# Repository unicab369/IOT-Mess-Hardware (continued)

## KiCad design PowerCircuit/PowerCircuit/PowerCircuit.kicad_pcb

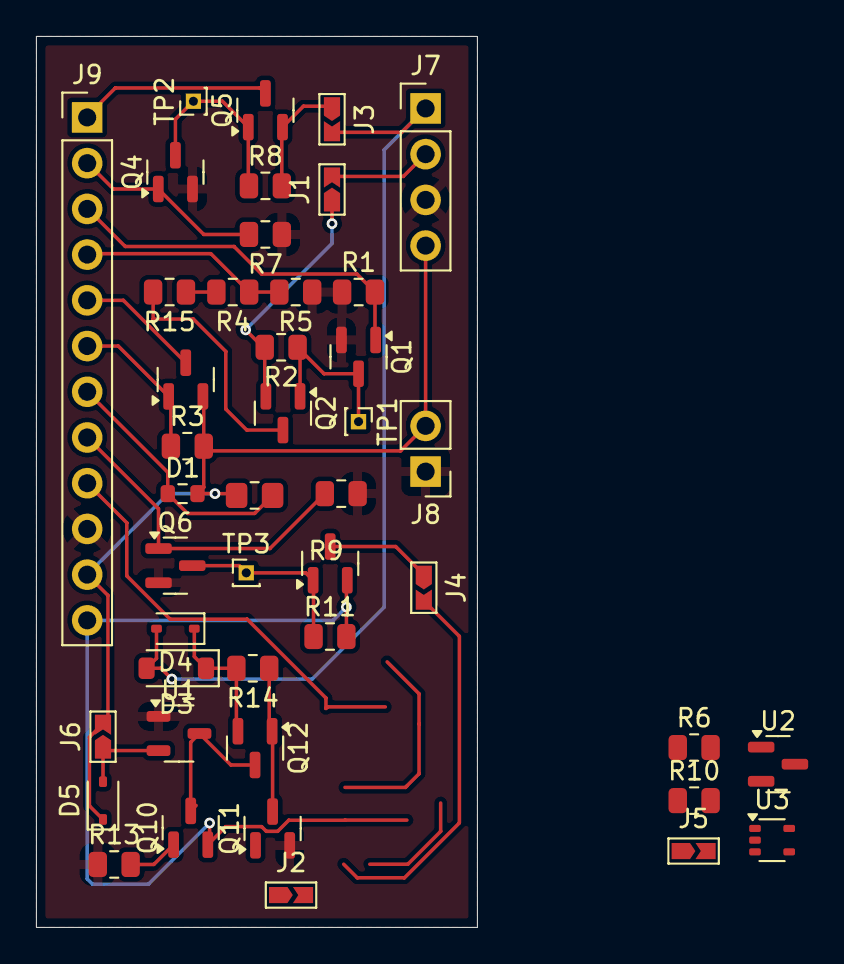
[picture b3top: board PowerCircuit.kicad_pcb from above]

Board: 2 copper layers, 24.5 x 49.5 mm, 44 parts (0 on the bottom side), 29 nets.

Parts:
D1: D_Photo; R_0603_1608Metric
D2: D_Photo; R_0805_2012Metric_Pad1.20x1.40mm_HandSolder
D3: MBR0520; D_SOD-123
D4, D5: BAT48JFILM; D_SOD-323
J1, J2, J3, J4, J5, J6: Jumper_2; Jumpper-triangle
J7: Conn_01x04_Pin; PinHeader_1x04_P2.54mm_Vertical
J8: Conn_01x02_Pin; PinHeader_1x02_P2.54mm_Vertical
J9: Conn_01x12_Pin; PinHeader_1x12_P2.54mm_Vertical
Q1, Q4, Q6, Q11: AO3400A; SOT-23
Q2, Q3, Q5, Q8, Q10, Q12: AO3401A (P-Fet); SOT-23
R1, R3, R7, R9, R10, R11, R13, R14: 100K; R_0805_2012Metric
R2, R4, R5, R6, R8, R15: 10K; R_0805_2012Metric
TP1, TP2, TP3: TestPoint; PinHeader_1x01_P1.00mm_Vertical
U1: XC6206PxxxMR; SOT-23-3
U2: LT431 (Voltage Ref); SOT-23
U3: 74LV1T08GW; SOT-353_SC-70-5

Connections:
+3V8: D1.2 (A), D2.2 (A), D5.1 (K), J6.2 (B), J7.4, J8.2, J9.11, Q3.2 (S), R3.2
ADC_LUX: D1.1 (K), D2.1 (K), J9.7
ADC_SOLAR: J9.4, R4.1, R5.2
GND: J7.3, J8.1, J9.10, Q1.2 (S), Q4.2 (S), Q6.2 (S), Q11.2 (S), R1.1, R5.1, R7.1, R9.1, R10.1, R13.1, U1.1 (GND), U2.3 (GND), U3.3 (GND)
IN-: D3.2 (A), D4.2 (A), J1.2 (B), J3.2 (B), J7.1
unnamed: D3.1 (K), D4.1 (K), Q12.2 (S), R14.2
unnamed: D5.2 (A), J6.1 (A), U1.2 (VO)
unnamed: J1.1 (A), Q2.2 (S), R2.2
unnamed: J2.1 (A), J5.2 (B), Q10.1 (G), R13.2
unnamed: J2.2 (B), J4.2 (B), Q11.1 (G)
unnamed: J3.1 (A), Q5.2 (S), R8.2
unnamed: J4.1 (A), Q8.3 (D)
unnamed: J5.1 (A), U3.4 (Y)
unnamed: Q1.3 (D), Q2.1 (G), R2.1, TP1.1
unnamed: Q2.3 (D), R15.2
unnamed: Q4.3 (D), Q5.1 (G), R8.1, TP2.1
unnamed: Q6.3 (D), Q8.1 (G), R11.1, TP3.1
unnamed: Q10.3 (D), Q12.3 (D), U1.3 (VI)
unnamed: Q11.3 (D), Q12.1 (G), R14.1
unnamed: R4.2, R15.1
unnamed: R6.2, U2.2 (VDD)
unnamed: R6.1, U2.1 (VOUT)
PWR_SENSORS: J9.5, Q3.3 (D)
SW_CHARGER: J9.2, Q4.1 (G), R7.2
SW_DIVIDER: J9.3, Q1.1 (G), R1.2
SW_PWR1: J9.8, Q6.1 (G), R9.2, R10.2, U3.2 (A)
SW_SENSORS: J9.6, Q3.1 (G), R3.1
TP4056_PWR: J9.1, Q5.3 (D)
VCC/BATT: J9.12, Q8.2 (S), Q10.2 (S), R11.2, U3.1 (B), U3.5 (VCC)

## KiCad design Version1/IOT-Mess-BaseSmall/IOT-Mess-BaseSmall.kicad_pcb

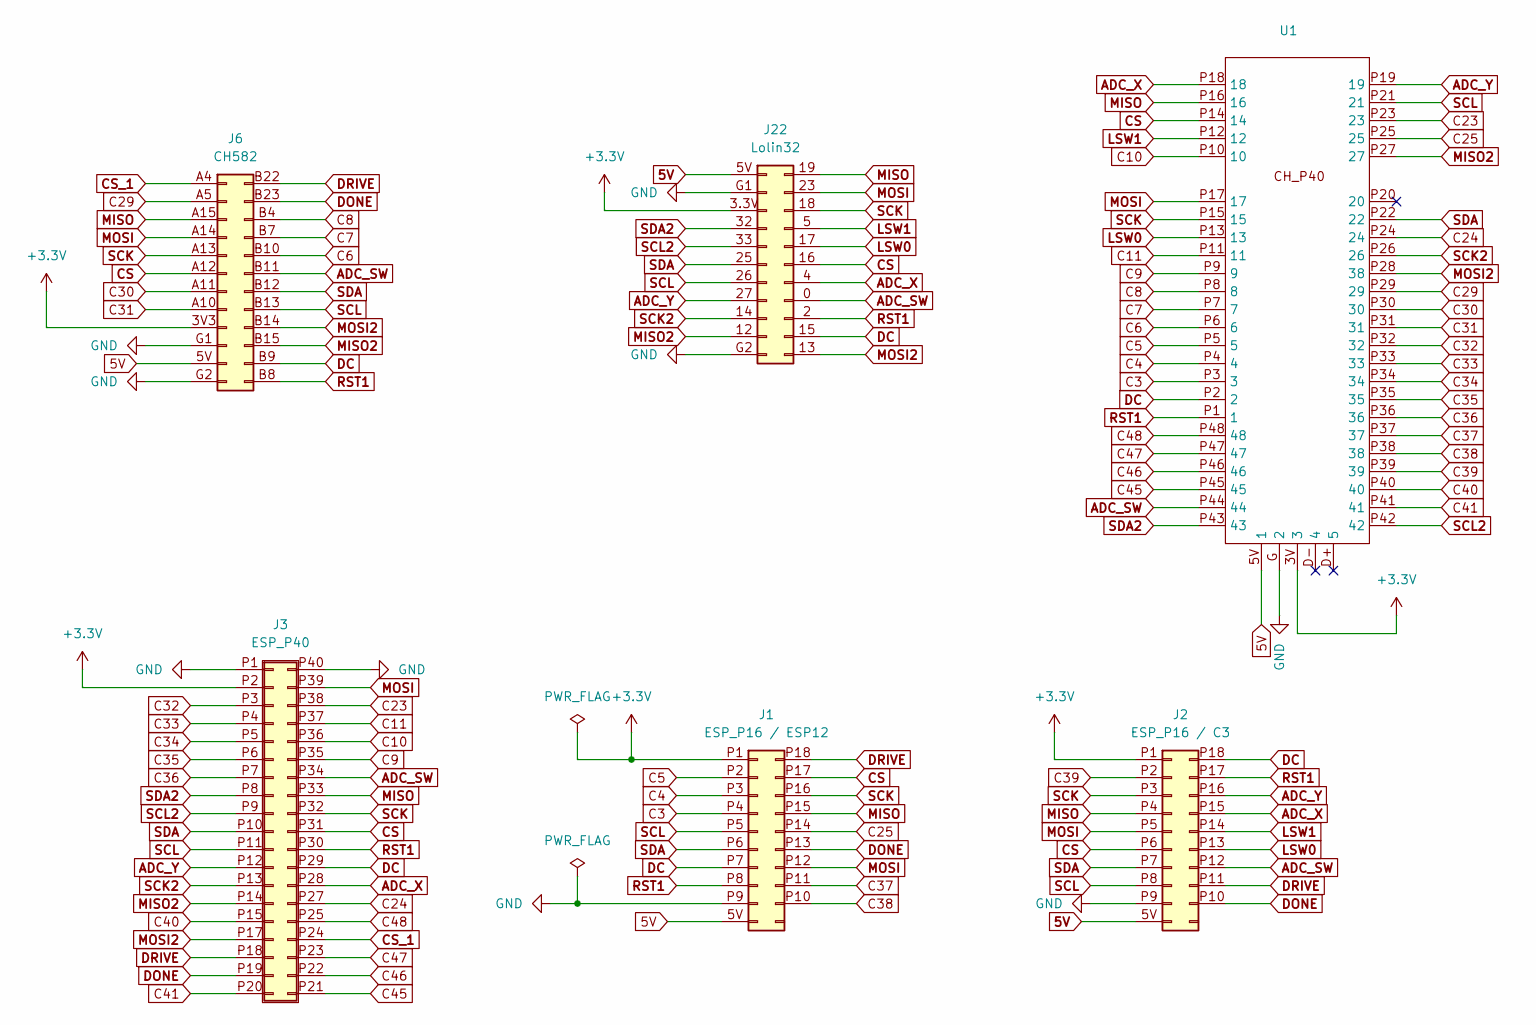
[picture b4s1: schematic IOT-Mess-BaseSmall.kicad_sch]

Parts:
J1: ESP_P16 / ESP12; ESP_P16
J2: ESP_P16 / C3; ESP_P16
J3: ESP_P40
J6: CH582; CH582_Base
J22: Lolin32; Lolin32-Adapter
U1: CH_P48

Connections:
5V: J1.5V (Pin_10), J2.5V (Pin_10), J6.5V (Pin_11), J22.5V (Pin_1), U1.5V (1)
+3.3V: J1.P1 (Pin_1), J2.P1 (Pin_1), J3.P2 (Pin_2), J6.3V3 (Pin_9), J22.3.3V (Pin_3), U1.3V (3)
ADC_SW: J2.P12 (Pin_14), J3.P34 (Pin_26), J6.B11 (Pin_18), J22.0 (Pin_19), U1.P44 (44)
ADC_X: J2.P15 (Pin_17), J3.P28 (Pin_32), J22.4 (Pin_18), U1.P18 (18)
ADC_Y: J2.P16 (Pin_18), J3.P12 (Pin_12), J22.27 (Pin_8), U1.P19 (19)
C3: J1.P4 (Pin_4), U1.P3 (3)
C4: J1.P3 (Pin_3), U1.P4 (4)
C5: J1.P2 (Pin_2), U1.P5 (5)
C6: J6.B10 (Pin_17), U1.P6 (6)
C7: J6.B7 (Pin_16), U1.P7 (7)
C8: J6.B4 (Pin_15), U1.P8 (8)
C9: J3.P35 (Pin_25), U1.P9 (9)
C10: J3.P36 (Pin_24), U1.P10 (10)
C11: J3.P37 (Pin_23), U1.P11 (11)
C23: J3.P38 (Pin_22), U1.P23 (23)
C24: J3.P27 (Pin_33), U1.P24 (24)
C25: J1.P14 (Pin_16), U1.P25 (25)
C29: J6.A5 (Pin_2), U1.P29 (29)
C30: J6.A11 (Pin_7), U1.P30 (30)
C31: J6.A10 (Pin_8), U1.P31 (31)
C32: J3.P3 (Pin_3), U1.P32 (32)
C33: J3.P4 (Pin_4), U1.P33 (33)
C34: J3.P5 (Pin_5), U1.P34 (34)
C35: J3.P6 (Pin_6), U1.P35 (35)
C36: J3.P7 (Pin_7), U1.P36 (36)
C37: J1.P11 (Pin_13), U1.P37 (37)
C38: J1.P10 (Pin_12), U1.P38 (38)
C39: J2.P2 (Pin_2), U1.P39 (39)
C40: J3.P15 (Pin_15), U1.P40 (40)
C41: J3.P20 (Pin_19), U1.P41 (41)
C45: J3.P21 (Pin_38), U1.P45 (45)
C46: J3.P22 (Pin_37), U1.P46 (46)
C47: J3.P23 (Pin_36), U1.P47 (47)
C48: J3.P25 (Pin_34), U1.P48 (48)
CS: J1.P17 (Pin_19), J2.P6 (Pin_6), J3.P31 (Pin_29), J6.A12 (Pin_6), J22.16 (Pin_17), U1.P14 (14)
CS_1: J3.P24 (Pin_35), J6.A4 (Pin_1)
DC: J1.P7 (Pin_7), J2.P18 (Pin_20), J3.P29 (Pin_31), J6.B9 (Pin_23), J22.15 (Pin_21), U1.P2 (2)
DONE: J1.P13 (Pin_15), J2.P10 (Pin_12), J3.P19 (Pin_18), J6.B23 (Pin_14)
DRIVE: J1.P18 (Pin_20), J2.P11 (Pin_13), J3.P18 (Pin_17), J6.B22 (Pin_13)
GND: J1.P9 (Pin_9), J2.P9 (Pin_9), J3.P1 (Pin_1), J3.P40 (Pin_20), J6.G1 (Pin_10), J6.G2 (Pin_12), J22.G1 (Pin_2), J22.G2 (Pin_11), U1.G (2)
LSW0: J2.P13 (Pin_15), J22.17 (Pin_16), U1.P13 (13)
LSW1: J2.P14 (Pin_16), J22.5 (Pin_15), U1.P12 (12)
MISO: J1.P15 (Pin_17), J2.P4 (Pin_4), J3.P33 (Pin_27), J6.A15 (Pin_3), J22.19 (Pin_12), U1.P16 (16)
MISO2: J3.P14 (Pin_14), J6.B15 (Pin_22), J22.12 (Pin_10), U1.P27 (27)
MOSI: J1.P12 (Pin_14), J2.P5 (Pin_5), J3.P39 (Pin_21), J6.A14 (Pin_4), J22.23 (Pin_13), U1.P17 (17)
MOSI2: J3.P17 (Pin_16), J6.B14 (Pin_21), J22.13 (Pin_22), U1.P28 (38)
RST1: J1.P8 (Pin_8), J2.P17 (Pin_19), J3.P30 (Pin_30), J6.B8 (Pin_24), J22.2 (Pin_20), U1.P1 (1)
SCK: J1.P16 (Pin_18), J2.P3 (Pin_3), J3.P32 (Pin_28), J6.A13 (Pin_5), J22.18 (Pin_14), U1.P15 (15)
SCK2: J3.P13 (Pin_13), J22.14 (Pin_9), U1.P26 (26)
SCL: J1.P5 (Pin_5), J2.P8 (Pin_8), J3.P11 (Pin_11), J6.B13 (Pin_20), J22.26 (Pin_7), U1.P21 (21)
SCL2: J3.P9 (Pin_9), J22.33 (Pin_5), U1.P42 (42)
SDA: J1.P6 (Pin_6), J2.P7 (Pin_7), J3.P10 (Pin_10), J6.B12 (Pin_19), J22.25 (Pin_6), U1.P22 (22)
SDA2: J3.P8 (Pin_8), J22.32 (Pin_4), U1.P43 (43)

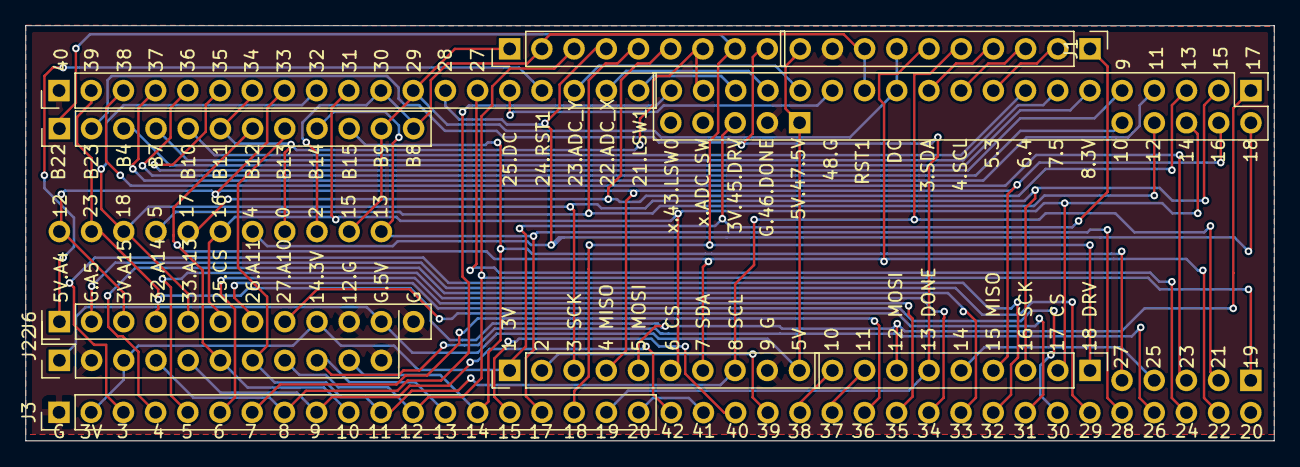
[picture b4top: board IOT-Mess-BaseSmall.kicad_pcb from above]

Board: 2 copper layers, 98.5 x 32.8 mm, 6 parts (0 on the bottom side), 53 nets.

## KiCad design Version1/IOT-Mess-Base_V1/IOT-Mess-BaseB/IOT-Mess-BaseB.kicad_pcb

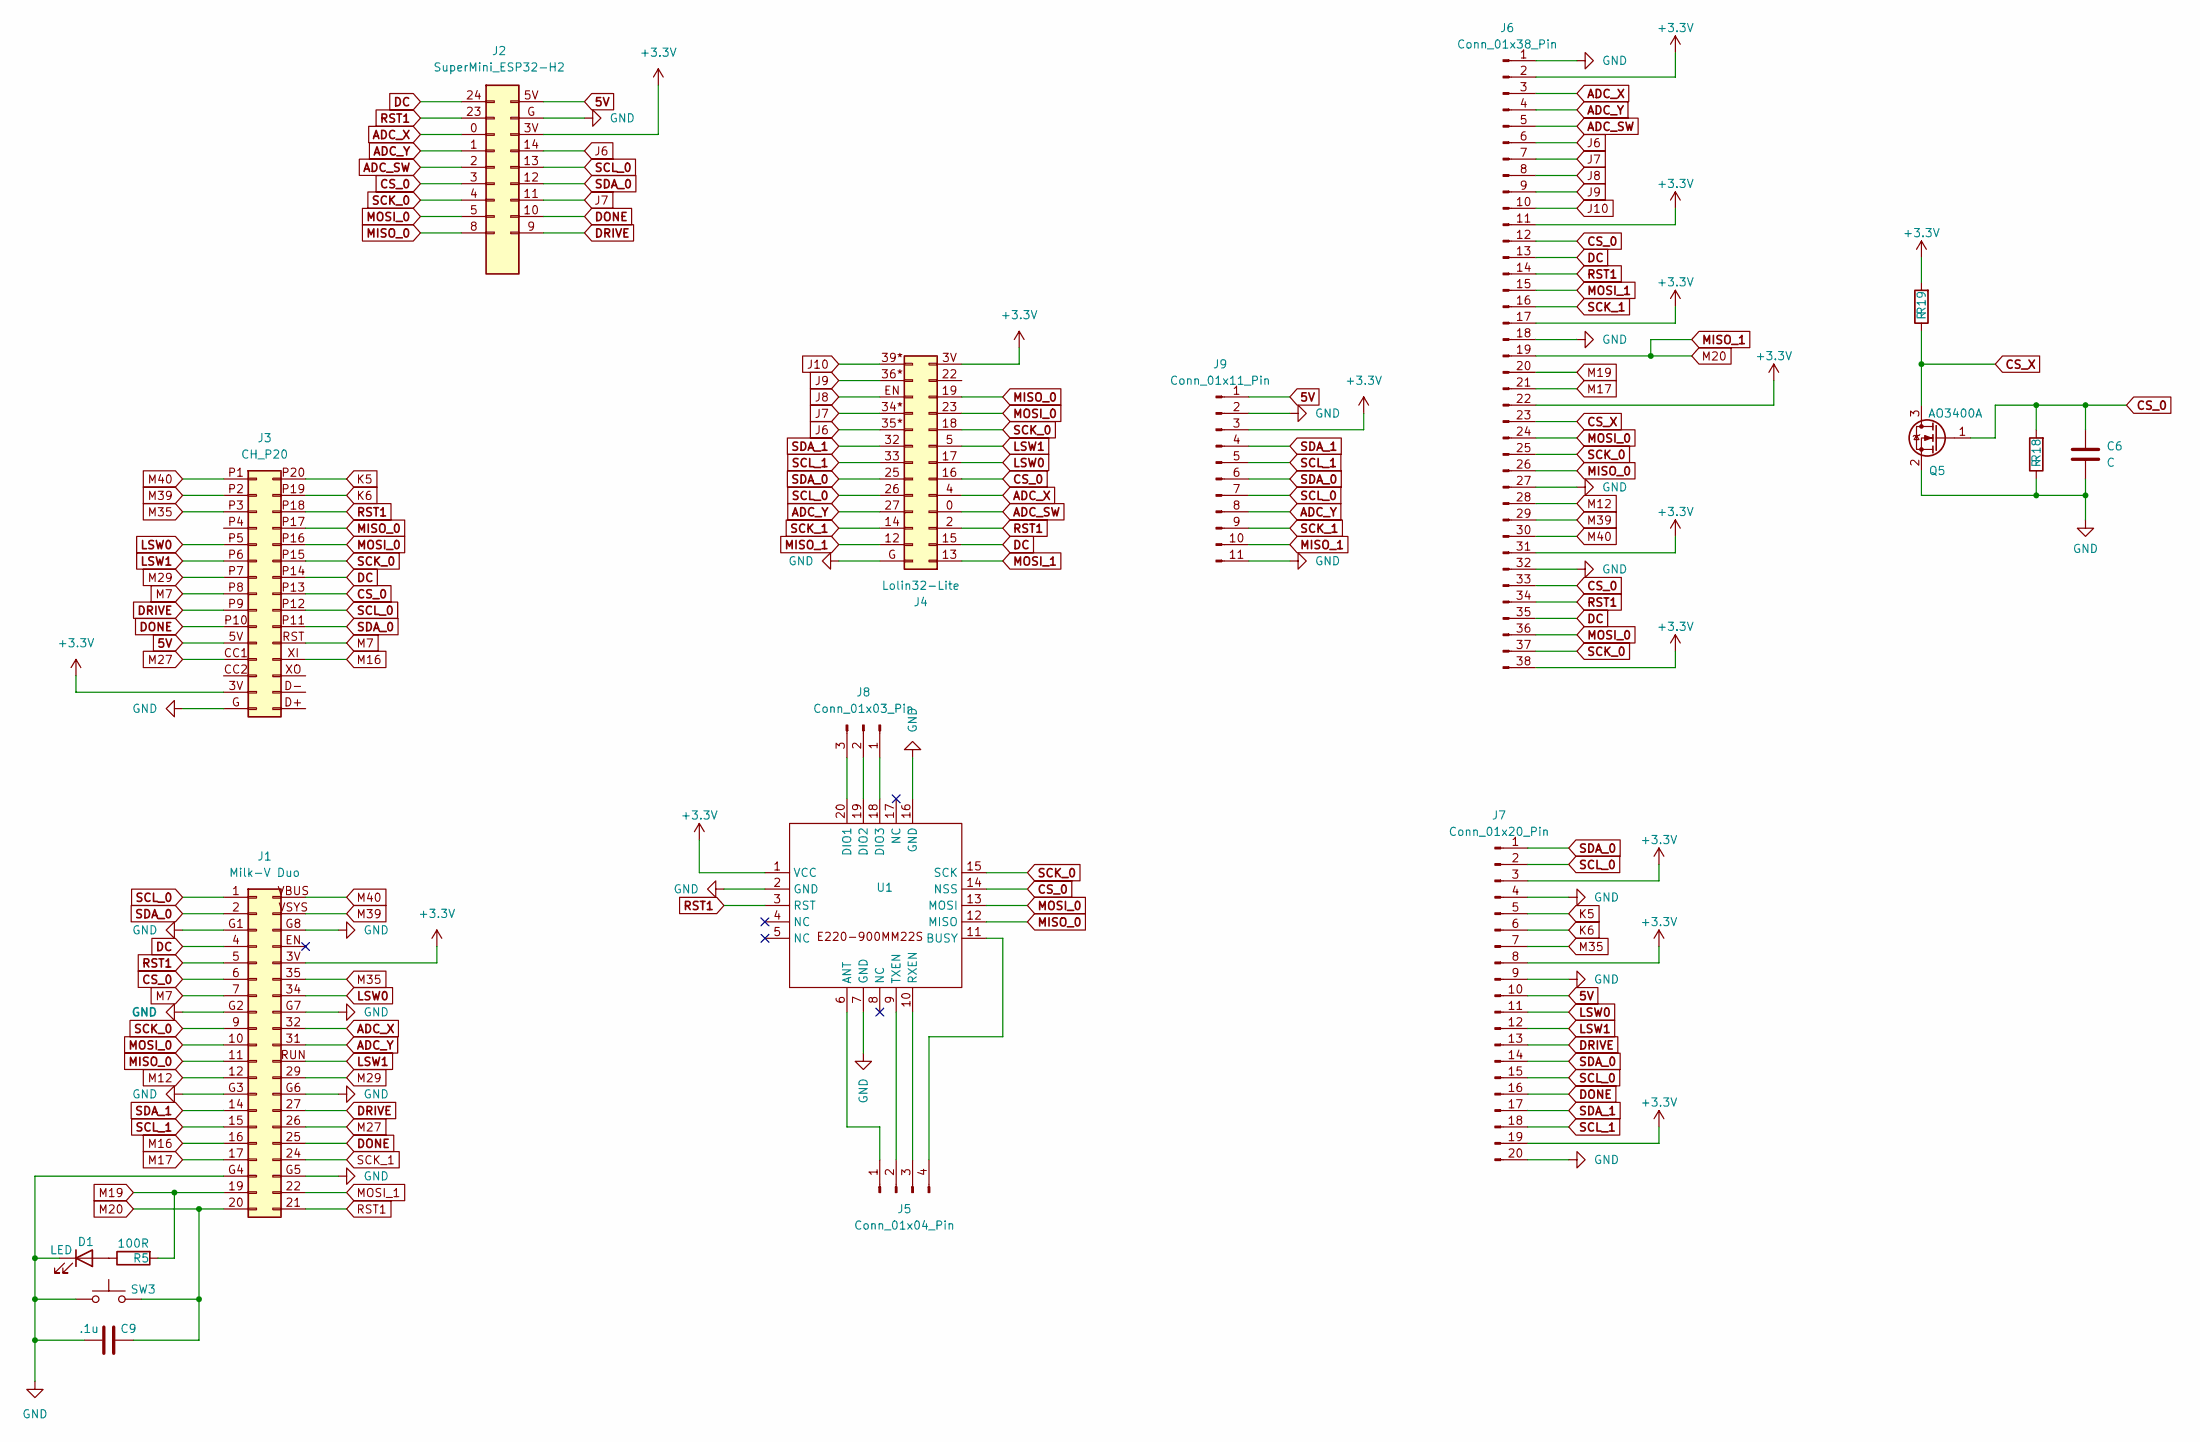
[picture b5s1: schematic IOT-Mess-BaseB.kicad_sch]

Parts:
C6: C; C_0603_1608Metric
C9: .1u; C_0603_1608Metric
D1: LED; LED_0603_1608Metric
J1: Milk-V Duo
J2: SuperMini_ESP32-H2; SuperMiniH2
J3: CH_P20
J4: Lolin32-Lite
J5: Conn_01x04_Pin; PinHeader_1x04_P1.27mm_Vertical
J6: Conn_01x38_Pin; PinHeader_1x38_P2.54mm_Vertical
J7: Conn_01x20_Pin; PinHeader_1x20_P2.54mm_Vertical
J8: Conn_01x03_Pin; PinHeader_1x03_P1.27mm_Vertical
J9: Conn_01x11_Pin; PinHeader_1x11_P2.54mm_Vertical
Q5: AO3400A; SOT-23
R5: 100R; R_0603_1608Metric
R18, R19: R; R_0603_1608Metric
SW3: SW_Push; SW_SPST_PTS810
U1: E220-900

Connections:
5V: J2.5V (Pin_18), J3.5V (Pin_11), J7.10, J9.1
+3.3V: J1.3V (Pin_36), J2.3V (Pin_16), J3.3V (Pin_14), J4.3V (Pin_13a), J6.2, J6.11, J6.17, J6.22, J6.31, J6.38, J7.3, J7.8, J7.19, J9.3, R19.2, U1.1 (VCC)
ADC_SW: J2.2 (Pin_5), J4.0 (Pin_4a), J6.5
ADC_X: J1.32, J2.0 (Pin_3), J4.4 (Pin_5a), J6.3
ADC_Y: J1.31, J2.1 (Pin_4), J4.27 (Pin_4b), J6.4, J9.8
CS_0: C6.1, J1.6, J2.3 (Pin_6), J3.P13 (Pin_23), J4.16 (Pin_6a), J6.12, J6.33, Q5.1 (G), R18.2, U1.14 (NSS)
CS_X: J6.23, Q5.3 (D), R19.1
DC: J1.4, J2.24 (Pin_1), J3.P14 (Pin_22), J4.15 (Pin_2a), J6.13, J6.35
DONE: J1.25, J2.10 (Pin_11), J3.P10 (Pin_10), J7.16
DRIVE: J1.27, J2.9 (Pin_10), J3.P9 (Pin_9), J7.13
GND: C6.2, C9.1, D1.1 (K), J1.G1 (Pin_3), J1.G2 (Pin_8), J1.G3 (Pin_13), J1.G4 (Pin_18), J1.G5 (Pin_23), J1.G6 (Pin_28), J1.G7 (Pin_33), J1.G8 (Pin_38), J2.G (Pin_17), J3.G (Pin_15), J4.G (Pin_1b), J6.1, J6.18, J6.27, J6.32, J7.4, J7.9, J7.20, J9.2, J9.11, Q5.2 (S), R18.1, SW3.2, U1.2 (GND), U1.7 (GND), U1.16 (GND)
J6: J2.14 (Pin_15), J4.35* (Pin_9b), J6.6
J7: J2.11 (Pin_12), J4.34* (Pin_10b), J6.7
J8: J4.EN (Pin_11b), J6.8
J9: J4.36* (Pin_12b), J6.9
J10: J4.39* (Pin_13b), J6.10
K5: J3.P20 (Pin_16), J7.5
K6: J3.P19 (Pin_17), J7.6
LSW0: J1.34, J2.26 (Pin_2), J3.P5 (Pin_5), J4.17 (Pin_7a), J7.11
LSW1: J1.RUN (Pin_30), J2.27 (Pin_1), J3.P6 (Pin_6), J4.5 (Pin_8a), J7.12
M7: J1.7, J3.P8 (Pin_8), J3.RST (Pin_26)
M12: J1.12, J6.28
M16: J1.16, J3.XI (Pin_27)
M17: J1.17, J6.21
M19: J1.19, J6.20, R5.2
M20: C9.2, J1.20, J4.12 (Pin_2b), J6.19, J9.10, SW3.1
M27: J1.26, J3.CC1 (Pin_12)
M29: J1.29, J3.P7 (Pin_7)
M35: J1.35, J3.P3 (Pin_3), J7.7
M39: J1.VSYS (Pin_39), J3.P2 (Pin_2), J6.29
M40: J1.VBUS (Pin_40), J3.P1 (Pin_1), J6.30
MISO_0: J1.11, J2.8 (Pin_9), J3.P17 (Pin_19), J4.19 (Pin_11a), J6.26, U1.12 (MISO)
MOSI_0: J1.10, J2.5 (Pin_8), J3.P16 (Pin_20), J4.23 (Pin_10a), J6.24, J6.36, U1.13 (MOSI)
MOSI_1: J1.22, J4.13 (Pin_1a), J6.15
unnamed: D1.2 (A), R5.1
unnamed: J5.1, U1.6 (ANT)
unnamed: J5.2, U1.9 (TXEN)
unnamed: J5.3, U1.10 (RXEN)
unnamed: J5.4, U1.11 (BUSY)
unnamed: J8.1, U1.18 (DIO3)
unnamed: J8.2, U1.19 (DIO2)
unnamed: J8.3, U1.20 (DIO1)
RST1: J1.5, J1.21, J2.23 (Pin_2), J3.P18 (Pin_18), J4.2 (Pin_3a), J6.14, J6.34, U1.3 (RST)
SCK_0: J1.9, J2.4 (Pin_7), J3.P15 (Pin_21), J4.18 (Pin_9a), J6.25, J6.37, U1.15 (SCK)
SCK_1: J1.24, J4.14 (Pin_3b), J6.16, J9.9
SCL_0: J1.1, J2.13 (Pin_14), J3.P12 (Pin_24), J4.26 (Pin_5b), J7.2, J7.15, J9.7
SCL_1: J1.15, J4.33 (Pin_7b), J7.18, J9.5
SDA_0: J1.2, J2.12 (Pin_13), J3.P11 (Pin_25), J4.25 (Pin_6b), J7.1, J7.14, J9.6
SDA_1: J1.14, J4.32 (Pin_8b), J7.17, J9.4

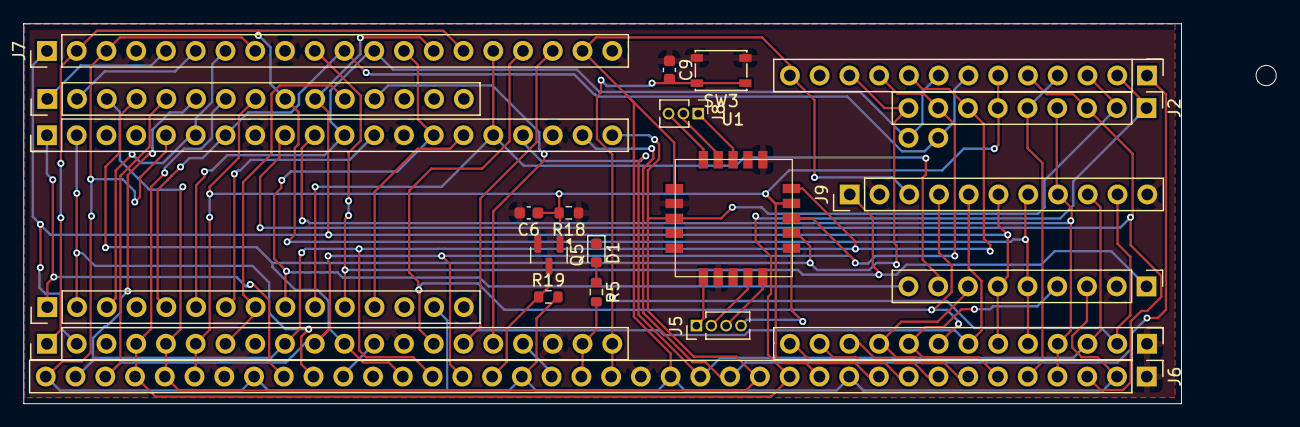
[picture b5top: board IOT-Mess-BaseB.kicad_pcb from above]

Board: 2 copper layers, 106.9 x 32.4 mm, 18 parts (0 on the bottom side), 49 nets.

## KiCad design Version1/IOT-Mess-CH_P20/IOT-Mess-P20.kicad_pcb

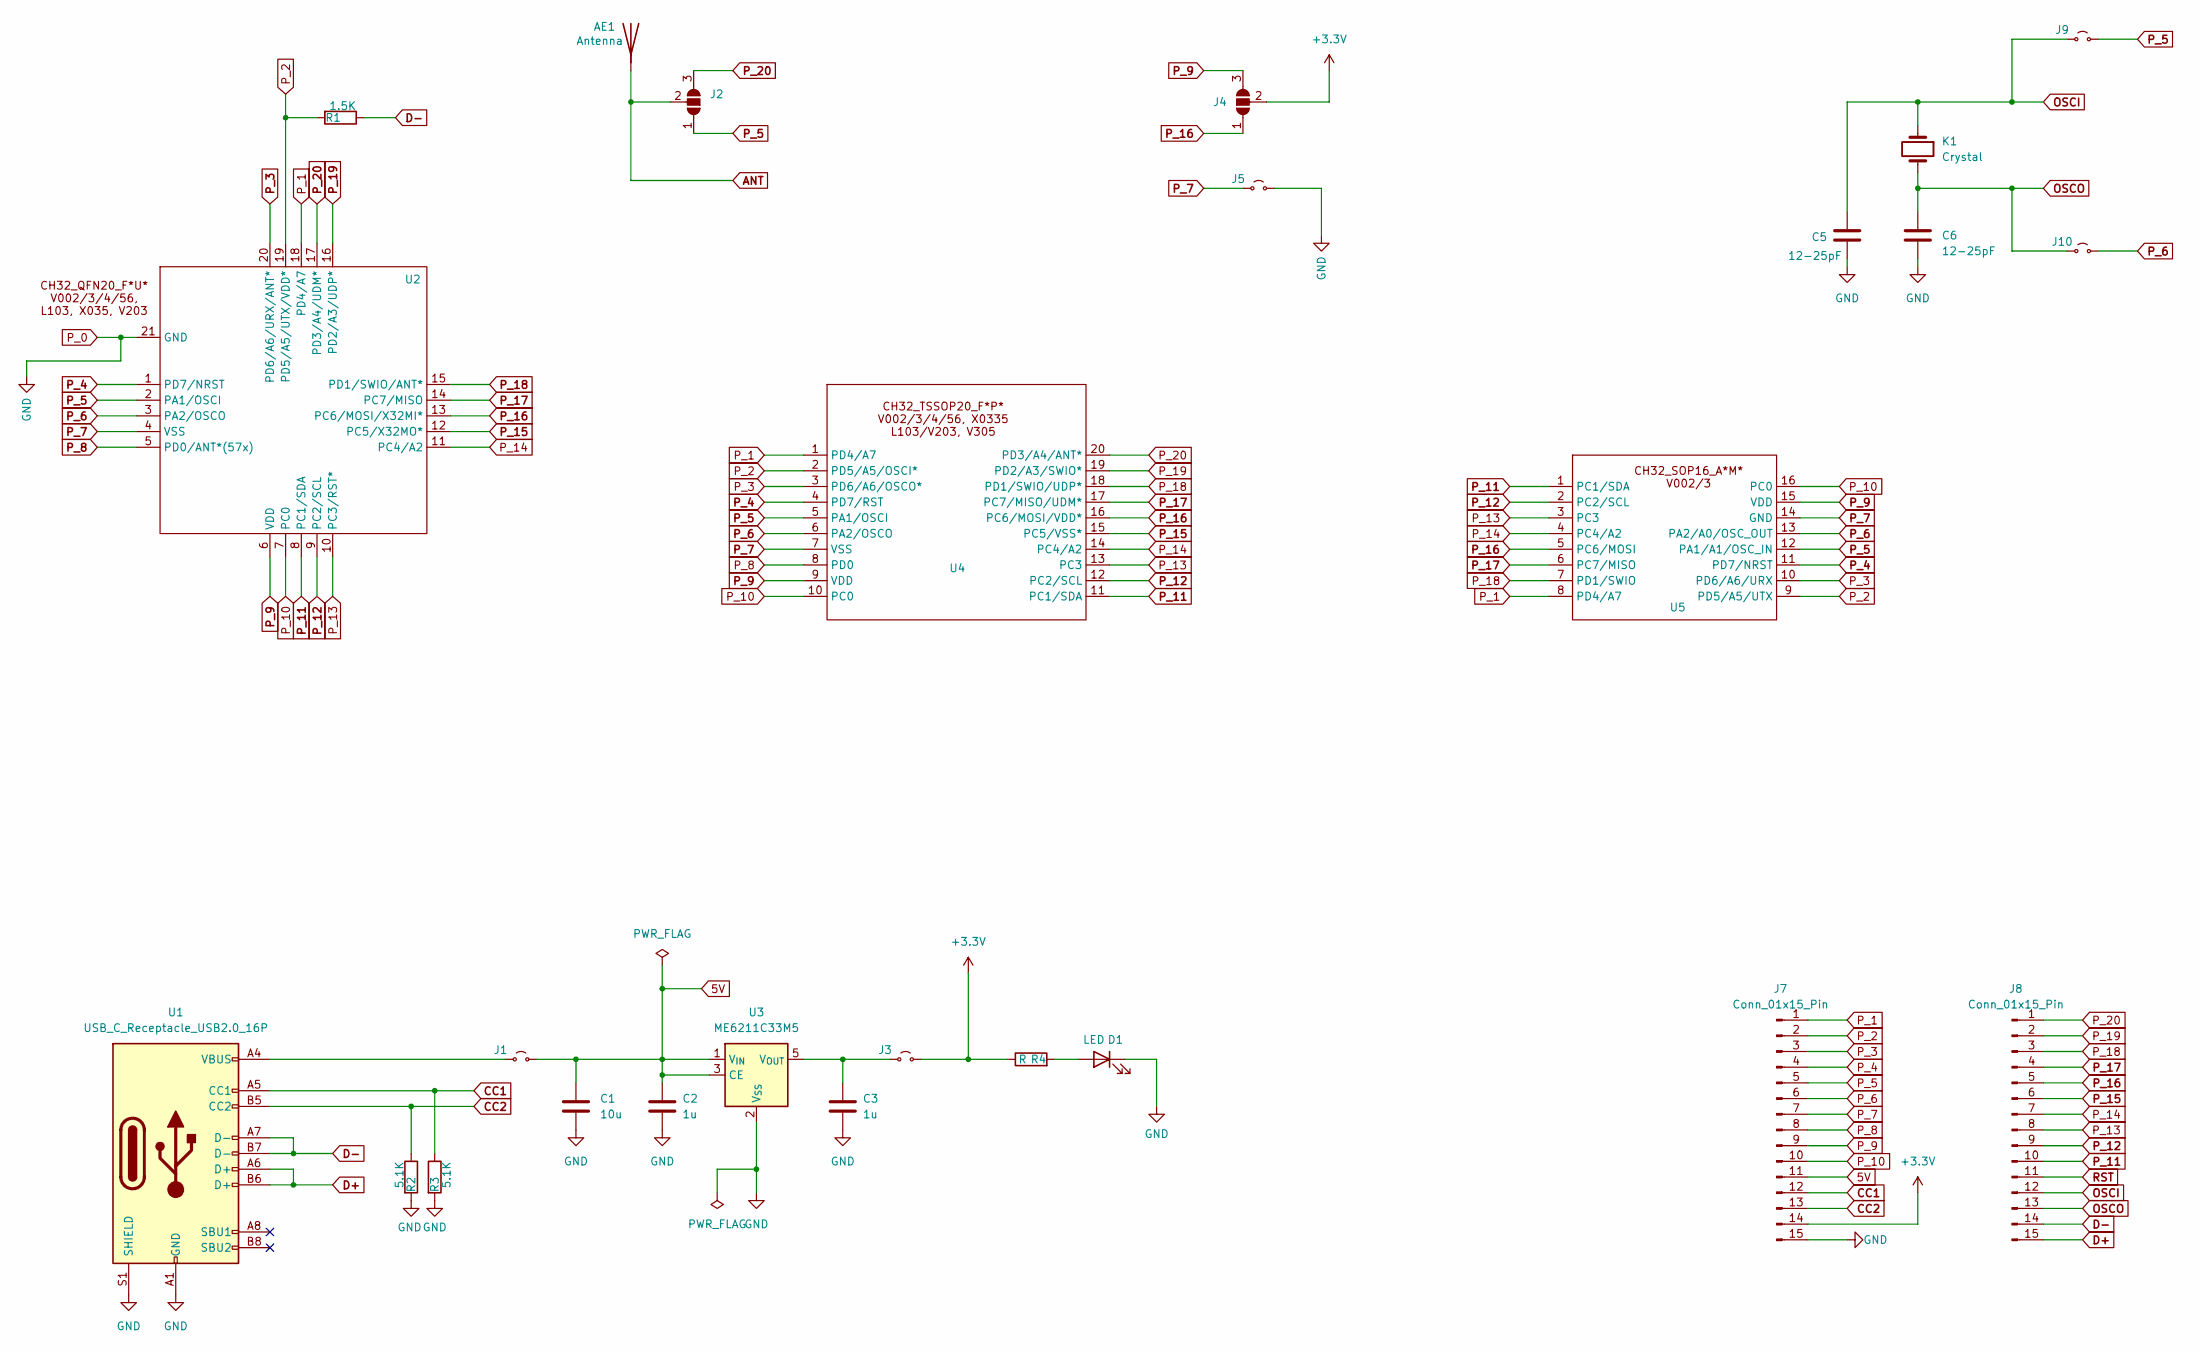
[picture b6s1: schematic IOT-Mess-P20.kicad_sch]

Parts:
AE1: Antenna; Texas_SWRA117D_2.4GHz_Right
C1: 10u; C_0603_1608Metric
C2, C3: 1u; C_0603_1608Metric
C5, C6: 12-25pF; C_0603_1608Metric
D1: LED; LED_0603_1608Metric
J1, J3, J5, J9, J10: Jumper_2; Jumpper-triangle
J2, J4: Jumper; Jumper-3_P1.3mm_Open_RoundedPad1.0x1.5mm
J7, J8: Conn_01x15_Pin; PinHeader_1x15_P2.54mm_Vertical
K1: Crystal; Crystal_SMD_3225-4Pin_3.2x2.5mm
R1: 1.5K; R_0603_1608Metric
R2, R3: 5.1K; R_0603_1608Metric
R4: R; R_0603_1608Metric
U1: USB_C_Receptacle_USB2.0_16P; USB_C_Receptacle_HRO_TYPE-C-31-M-12
U2: QFN-20-1EP_3x3mm_P0.4mm_EP1.65x1.65mm_ThermalVias
U3: ME6211C33M5; SOT-23-5
U4: TSSOP-20_4.4x6.5mm_P0.65mm
U5: SOP-16_3.9x9.9mm_P1.27mm

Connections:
5V: C1.1, C2.1, J1.2 (B), J7.11, U3.1 (V_{IN}), U3.3 (CE)
+3.3V: J3.2 (B), J4.2 (C), J7.14, R4.1
ANT: AE1.1 (A), J2.2 (C)
CC1: J7.12, R3.1, U1.A5 (CC1)
CC2: J7.13, R2.1, U1.B5 (CC2)
D+: J8.15, U1.A6 (D+), U1.B6 (D+)
D-: J8.14, R1.1, U1.A7 (D-), U1.B7 (D-)
unnamed: D1.2 (A), R4.2
unnamed: J1.1 (A), U1.A4 (VBUS), U1.A9 (VBUS), U1.B4 (VBUS), U1.B9 (VBUS)
unnamed: C3.1, J3.1 (A), U3.5 (V_{OUT})
OSCI: C5.1, J8.12, J9.1 (A), K1.1
OSCO: C6.1, J8.13, J10.1 (A), K1.2
P_0: C1.2, C2.2, C3.2, C5.2, C6.2, D1.1 (K), J5.2 (B), J7.15, R2.2, R3.2, U1.A1 (GND), U1.A12 (GND), U1.B1 (GND), U1.B12 (GND), U1.S1 (SHIELD), U2.21 (GND), U3.2 (V_{SS})
P_1: J7.1, U2.18 (PD4/A7), U4.1 (PD4/A7), U5.8 (PD4/A7)
P_2: J7.2, R1.2, U2.19 (PD5/A5/UTX/VDD*), U4.2 (PD5/A5/OSCI*), U5.9 (PD5/A5/UTX)
P_3: J7.3, U2.20 (PD6/A6/URX/ANT*), U4.3 (PD6/A6/OSCO*), U5.10 (PD6/A6/URX)
P_4: J7.4, U2.1 (PD7/NRST), U4.4 (PD7/RST), U5.11 (PD7/NRST)
P_5: J2.1 (A), J7.5, J9.2 (B), U2.2 (PA1/OSCI), U4.5 (PA1/OSCI), U5.12 (PA1/A1/OSC_IN)
P_6: J7.6, J10.2 (B), U2.3 (PA2/OSCO), U4.6 (PA2/OSCO), U5.13 (PA2/A0/OSC_OUT)
P_7: J5.1 (A), J7.7, U2.4 (VSS), U4.7 (VSS), U5.14 (GND)
P_8: J7.8, U2.5 (PD0/ANT*(57x)), U4.8 (PD0)
P_9: J4.3 (B), J7.9, U2.6 (VDD), U4.9 (VDD), U5.15 (VDD)
P_10: J7.10, U2.7 (PC0), U4.10 (PC0), U5.16 (PC0)
P_11: J8.10, U2.8 (PC1/SDA), U4.11 (PC1/SDA), U5.1 (PC1/SDA)
P_12: J8.9, U2.9 (PC2/SCL), U4.12 (PC2/SCL), U5.2 (PC2/SCL)
P_13: J8.8, U2.10 (PC3/RST*), U4.13 (PC3), U5.3 (PC3)
P_14: J8.7, U2.11 (PC4/A2), U4.14 (PC4/A2), U5.4 (PC4/A2)
P_15: J8.6, U2.12 (PC5/X32MO*), U4.15 (PC5/VSS*)
P_16: J4.1 (A), J8.5, U2.13 (PC6/MOSI/X32MI*), U4.16 (PC6/MOSI/VDD*), U5.5 (PC6/MOSI)
P_17: J8.4, U2.14 (PC7/MISO), U4.17 (PC7/MISO/UDM*), U5.6 (PC7/MISO)
P_18: J8.3, U2.15 (PD1/SWIO/ANT*), U4.18 (PD1/SWIO/UDP*), U5.7 (PD1/SWIO)
P_19: J8.2, U2.16 (PD2/A3/UDP*), U4.19 (PD2/A3/SWIO*)
P_20: J2.3 (B), J8.1, U2.17 (PD3/A4/UDM*), U4.20 (PD3/A4/ANT*)
RST: J8.11

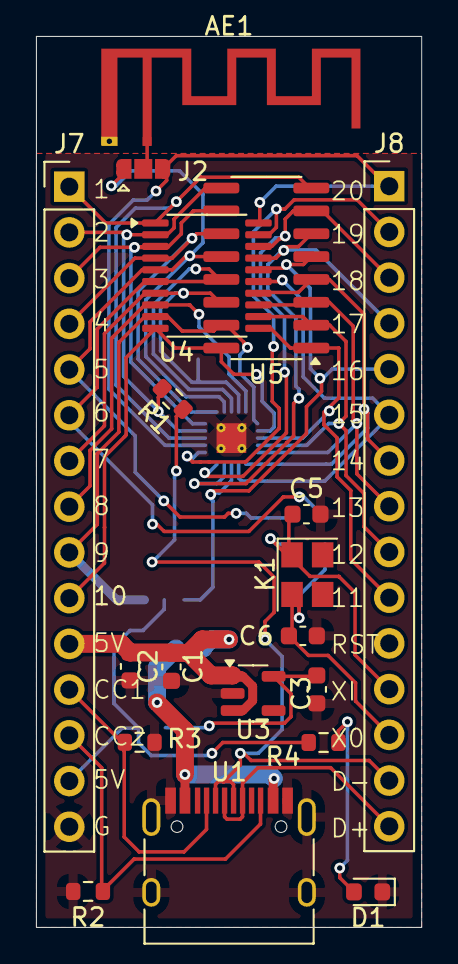
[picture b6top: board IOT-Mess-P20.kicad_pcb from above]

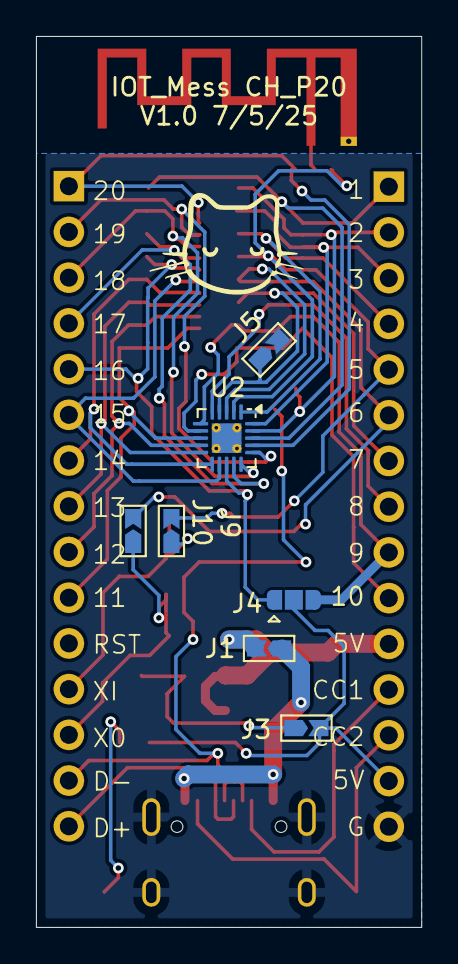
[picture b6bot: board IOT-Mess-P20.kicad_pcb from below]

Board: 2 copper layers, 21.4 x 49.5 mm, 26 parts (7 on the bottom side), 33 nets.

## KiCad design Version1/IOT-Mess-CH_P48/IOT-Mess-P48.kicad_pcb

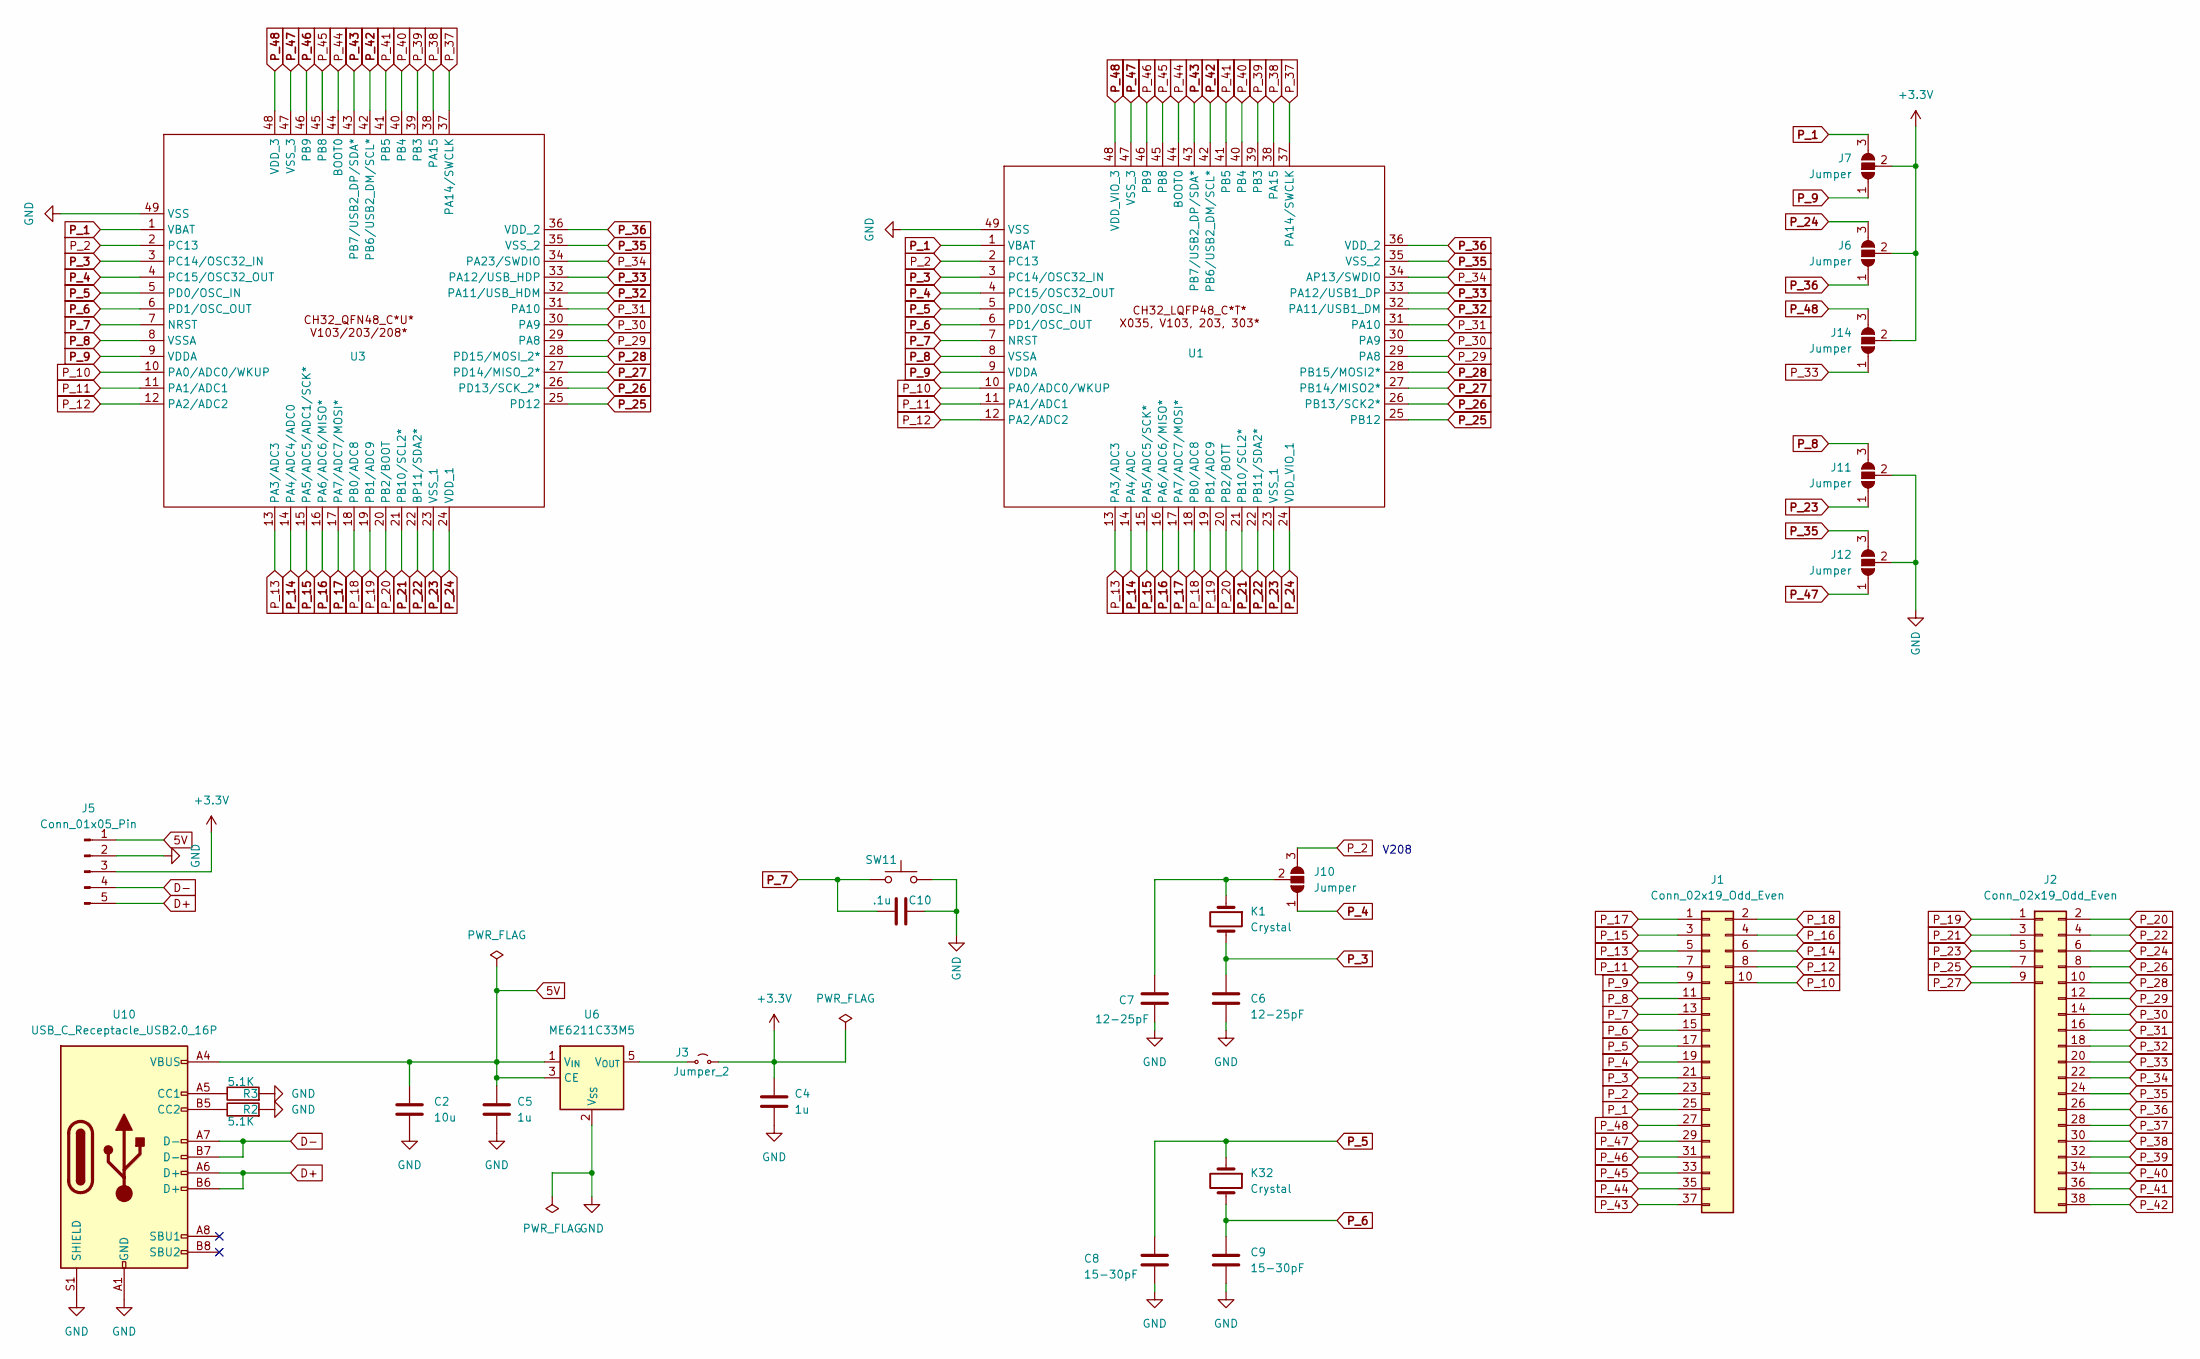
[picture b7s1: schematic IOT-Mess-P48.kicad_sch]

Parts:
C2: 10u; C_0603_1608Metric
C4, C5: 1u; C_0603_1608Metric
C6, C7: 12-25pF; C_0603_1608Metric
C8, C9: 15-30pF; C_0603_1608Metric
C10: .1u; C_0603_1608Metric
J1, J2: Conn_02x19_Odd_Even; PinHeader_2x19_P2.54mm_Vertical
J3: Jumper_2; Jumpper-triangle
J5: Conn_01x05_Pin; PinHeader_1x05_P2.54mm_Vertical
J6, J7, J10, J11, J12, J14: Jumper; Jumper-3_P1.3mm_Open_RoundedPad1.0x1.5mm
K1, K32: Crystal; Crystal_SMD_3225-4Pin_3.2x2.5mm
R2, R3: 5.1K; R_0603_1608Metric
SW11: SW_Push; SW_SPST_PTS810
U1: LQFP-48-1EP_7x7mm_P0.5mm_EP3.6x3.6mm
U3: CH32L103C8T6; QFN-48-1EP_5x5mm_P0.35mm_EP3.7x3.7mm_ThermalVias
U6: ME6211C33M5; SOT-23-5
U10: USB_C_Receptacle_USB2.0_16P; USB_C_Receptacle_HRO_TYPE-C-31-M-12

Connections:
5V: C2.1, C5.1, J5.1, U6.1 (V_{IN}), U6.3 (CE), U10.A4 (VBUS), U10.A9 (VBUS), U10.B4 (VBUS), U10.B9 (VBUS)
+3.3V: C4.1, J3.2 (B), J5.3, J6.2 (C), J7.2 (C), J14.2 (C)
D+: J5.5, U10.A6 (D+), U10.B6 (D+)
D-: J5.4, U10.A7 (D-), U10.B7 (D-)
GND: C2.2, C4.2, C5.2, C6.2, C7.2, C8.2, C9.2, C10.2, J5.2, J11.2 (C), J12.2 (C), R2.2, R3.2, SW11.2, U1.49 (VSS), U3.49 (VSS), U6.2 (V_{SS}), U10.A1 (GND), U10.A12 (GND), U10.B1 (GND), U10.B12 (GND), U10.S1 (SHIELD)
unnamed: J3.1 (A), U6.5 (V_{OUT})
unnamed: C7.1, J10.2 (C), K1.1
unnamed: R3.1, U10.A5 (CC1)
unnamed: R2.1, U10.B5 (CC2)
P_1: J1.25, J7.3 (B), U1.1 (VBAT), U3.1 (VBAT)
P_2: J1.23, J10.3 (B), U1.2 (PC13), U3.2 (PC13)
P_3: C6.1, J1.21, K1.2, U1.3 (PC14/OSC32_IN), U3.3 (PC14/OSC32_IN)
P_4: J1.19, J10.1 (A), U1.4 (PC15/OSC32_OUT), U3.4 (PC15/OSC32_OUT)
P_5: C8.1, J1.17, K32.1, U1.5 (PD0/OSC_IN), U3.5 (PD0/OSC_IN)
P_6: C9.1, J1.15, K32.2, U1.6 (PD1/OSC_OUT), U3.6 (PD1/OSC_OUT)
P_7: C10.1, J1.13, SW11.1, U1.7 (NRST), U3.7 (NRST)
P_8: J1.11, J11.3 (B), U1.8 (VSSA), U3.8 (VSSA)
P_9: J1.9, J7.1 (A), U1.9 (VDDA), U3.9 (VDDA)
P_10: J1.10, U1.10 (PA0/ADC0/WKUP), U3.10 (PA0/ADC0/WKUP)
P_11: J1.7, U1.11 (PA1/ADC1), U3.11 (PA1/ADC1)
P_12: J1.8, U1.12 (PA2/ADC2), U3.12 (PA2/ADC2)
P_13: J1.5, U1.13 (PA3/ADC3), U3.13 (PA3/ADC3)
P_14: J1.6, U1.14 (PA4/ADC), U3.14 (PA4/ADC4/ADC0)
P_15: J1.3, U1.15 (PA5/ADC5/SCK*), U3.15 (PA5/ADC5/ADC1/SCK*)
P_16: J1.4, U1.16 (PA6/ADC6/MISO*), U3.16 (PA6/ADC6/MISO*)
P_17: J1.1, U1.17 (PA7/ADC7/MOSI*), U3.17 (PA7/ADC7/MOSI*)
P_18: J1.2, U1.18 (PB0/ADC8), U3.18 (PB0/ADC8)
P_19: J2.1, U1.19 (PB1/ADC9), U3.19 (PB1/ADC9)
P_20: J2.2, U1.20 (PB2/BOTT), U3.20 (PB2/BOOT)
P_21: J2.3, U1.21 (PB10/SCL2*), U3.21 (PB10/SCL2*)
P_22: J2.4, U1.22 (PB11/SDA2*), U3.22 (BP11/SDA2*)
P_23: J2.5, J11.1 (A), U1.23 (VSS_1), U3.23 (VSS_1)
P_24: J2.6, J6.3 (B), U1.24 (VDD_VIO_1), U3.24 (VDD_1)
P_25: J2.7, U1.25 (PB12), U3.25 (PD12)
P_26: J2.8, U1.26 (PB13/SCK2*), U3.26 (PD13/SCK_2*)
P_27: J2.9, U1.27 (PB14/MISO2*), U3.27 (PD14/MISO_2*)
P_28: J2.10, U1.28 (PB15/MOSI2*), U3.28 (PD15/MOSI_2*)
P_29: J2.12, U1.29 (PA8), U3.29 (PA8)
P_30: J2.14, U1.30 (PA9), U3.30 (PA9)
P_31: J2.16, U1.31 (PA10), U3.31 (PA10)
P_32: J2.18, U1.32 (PA11/USB1_DM), U3.32 (PA11/USB_HDM)
P_33: J2.20, J14.1 (A), U1.33 (PA12/USB1_DP), U3.33 (PA12/USB_HDP)
P_34: J2.22, U1.34 (AP13/SWDIO), U3.34 (PA23/SWDIO)
P_35: J2.24, J12.3 (B), U1.35 (VSS_2), U3.35 (VSS_2)
P_36: J2.26, J6.1 (A), U1.36 (VDD_2), U3.36 (VDD_2)
P_37: J2.28, U1.37 (PA14/SWCLK), U3.37 (PA14/SWCLK)
P_38: J2.30, U1.38 (PA15), U3.38 (PA15)
P_39: J2.32, U1.39 (PB3), U3.39 (PB3)
P_40: J2.34, U1.40 (PB4), U3.40 (PB4)
P_41: J2.36, U1.41 (PB5), U3.41 (PB5)
P_42: J2.38, U1.42 (PB6/USB2_DM/SCL*), U3.42 (PB6/USB2_DM/SCL*)
P_43: J1.37, U1.43 (PB7/USB2_DP/SDA*), U3.43 (PB7/USB2_DP/SDA*)
P_44: J1.35, U1.44 (BOOT0), U3.44 (BOOT0)
P_45: J1.33, U1.45 (PB8), U3.45 (PB8)
P_46: J1.31, U1.46 (PB9), U3.46 (PB9)
P_47: J1.29, J12.1 (A), U1.47 (VSS_3), U3.47 (VSS_3)
P_48: J1.27, J14.3 (B), U1.48 (VDD_VIO_3), U3.48 (VDD_3)

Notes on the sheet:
V208
